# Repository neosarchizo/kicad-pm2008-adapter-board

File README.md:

# kicad-pm2008-adapter-board
[KiCAD][CUBIC] PM2008 Adapter Board

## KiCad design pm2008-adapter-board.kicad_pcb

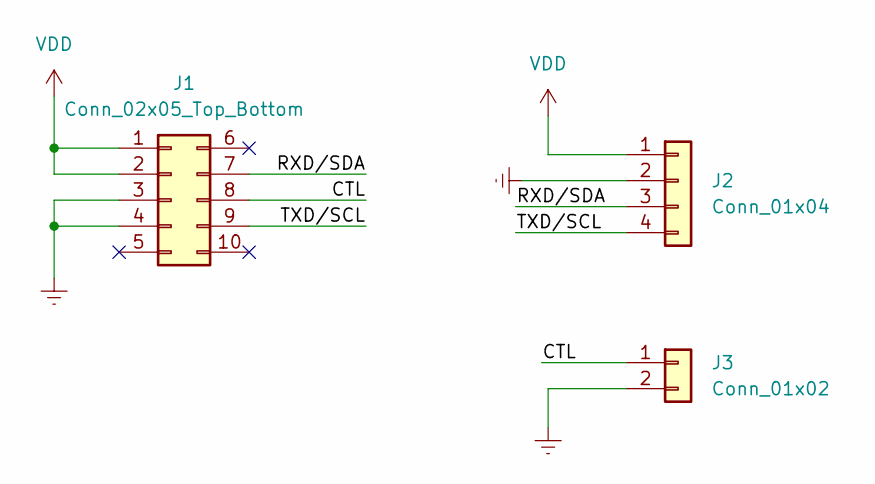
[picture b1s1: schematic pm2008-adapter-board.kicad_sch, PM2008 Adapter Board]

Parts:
J1: Conn_02x05_Top_Bottom
J2: Conn_01x04; PinHeader_1x04_P2.54mm_Vertical
J3: Conn_01x02; PinHeader_1x02_P2.54mm_Vertical

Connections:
/CTL: J1.8, J3.1
/RXD/SDA: J1.7, J2.3
/TXD/SCL: J1.9, J2.4
Earth: J1.3, J1.4, J2.2, J3.2
VDD: J1.1, J1.2, J2.1

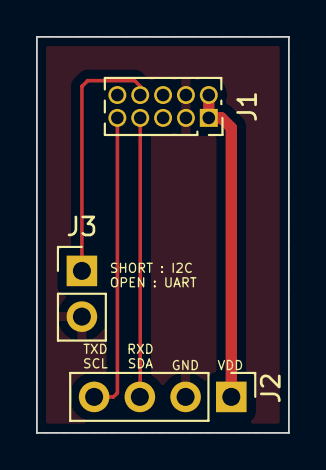
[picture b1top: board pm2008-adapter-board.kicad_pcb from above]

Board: 2 copper layers, 14.0 x 22.0 mm, 3 parts (0 on the bottom side), 5 nets.

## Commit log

2022-10-21 chore: update .gitignore
2022-10-21 feat: add initial KiCAD files
2022-10-24 feat: update schematic
2022-10-28 feat: update artwork
2022-10-31 feat: update component
